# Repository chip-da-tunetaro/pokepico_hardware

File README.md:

# pokepico_hardware_MFT2019
pokepico rev.1のハードウェア

## 回路図
schematics.pdfを参照してください

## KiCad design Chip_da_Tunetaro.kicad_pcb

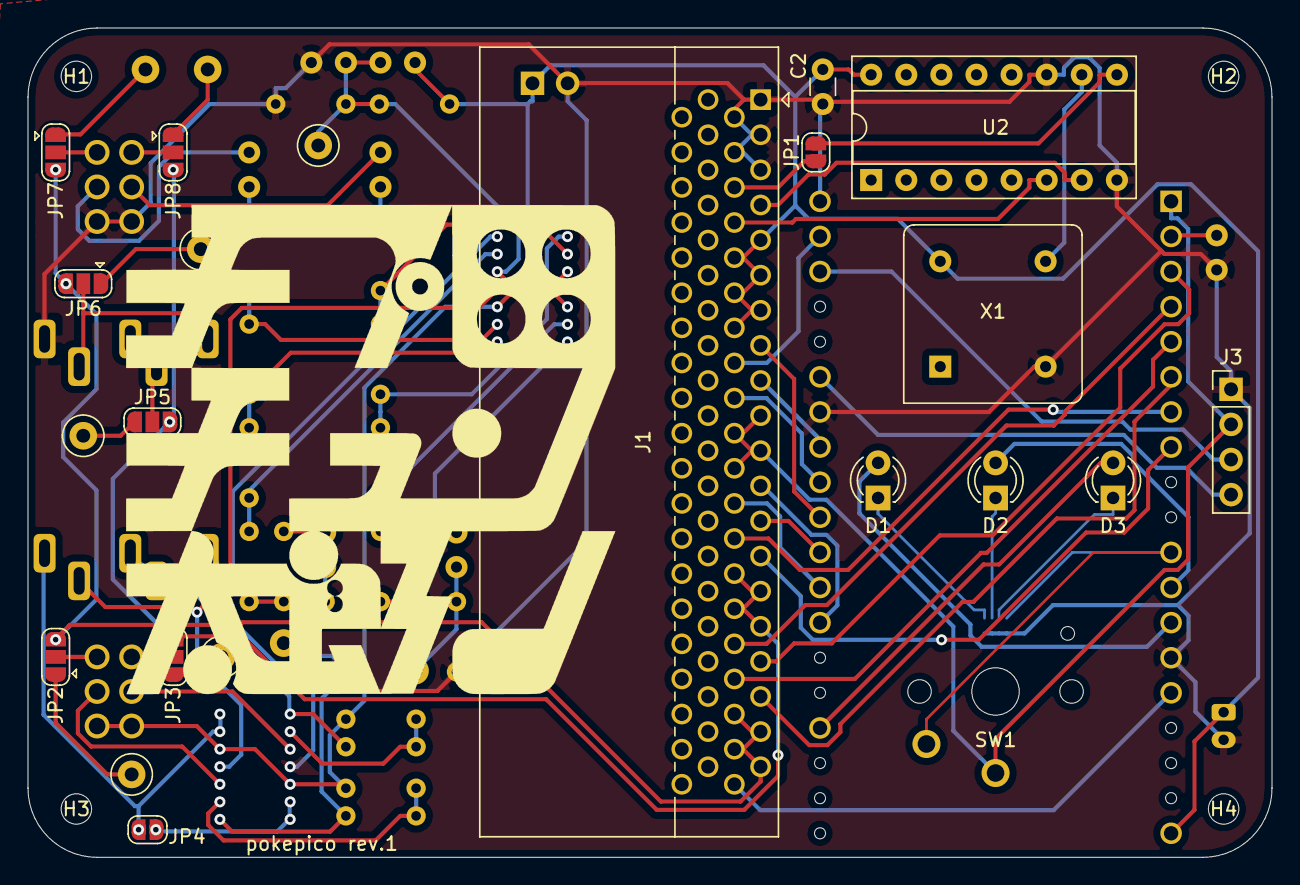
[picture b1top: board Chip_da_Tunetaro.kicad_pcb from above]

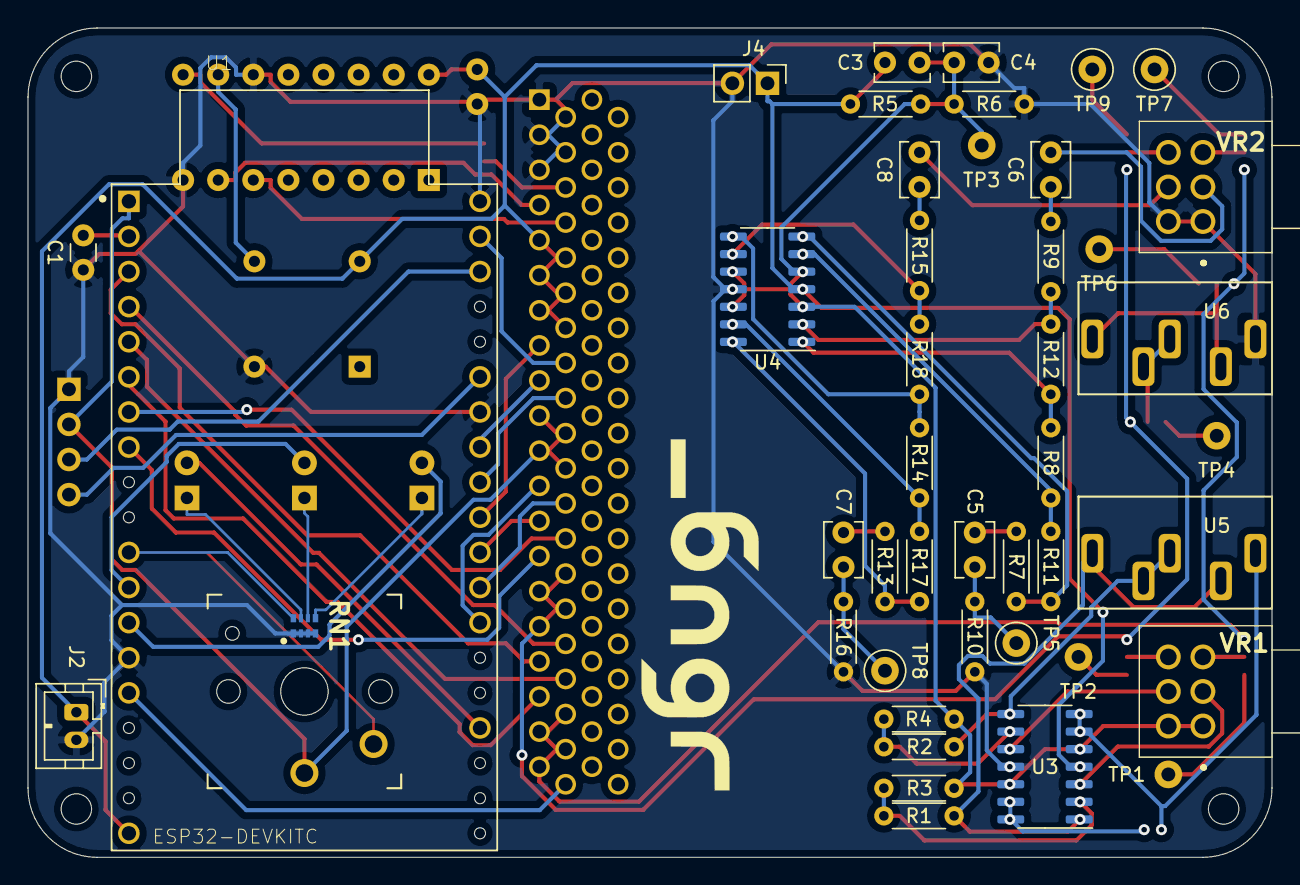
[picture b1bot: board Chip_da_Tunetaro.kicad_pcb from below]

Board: 2 copper layers, 90.0 x 60.0 mm, 66 parts (39 on the bottom side), 71 nets.

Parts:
C1: 1n; C_Disc_D3.0mm_W1.6mm_P2.50mm
C2: 0.1u; C_Disc_D3.0mm_W1.6mm_P2.50mm
C3, C4, C5, C6, C7, C8: C; C_Disc_D3.8mm_W2.6mm_P2.50mm
D1, D2, D3: LED; LED_D3.0mm
H1, H2, H3, H4: MountingHole; MountingHole_2.2mm_M2
J1: microbit_edge_connector; 4UCON_10156_2x40_P1.27mm_Socket_Horizontal
J2: Conn_01x02_Male; JST_PH_B2B-PH-K_1x02_P2.00mm_Vertical
J3: I2C; PinHeader_1x04_P2.54mm_Vertical
J4: POWERPOINT; PinHeader_1x02_P2.54mm_Vertical
JP1: SAA_INT_CLOCK; SolderJumper-2_P1.3mm_Open_RoundedPad1.0x1.5mm
JP2: FROW_L_SEL; SolderJumper-3_P1.3mm_Open_RoundedPad1.0x1.5mm
JP3: FLOW_R_SEL; SolderJumper-3_P1.3mm_Open_RoundedPad1.0x1.5mm
JP4: Jumper_NO_Small; SolderJumper-2_P1.3mm_Open_RoundedPad1.0x1.5mm
JP5: OUT_R_SEL; SolderJumper-3_P1.3mm_Open_RoundedPad1.0x1.5mm
JP6: OUT_L_SEL; SolderJumper-3_P1.3mm_Open_RoundedPad1.0x1.5mm
JP7: AMP_L_SEL; SolderJumper-3_P1.3mm_Open_RoundedPad1.0x1.5mm
JP8: AMP_R_SEL; SolderJumper-3_P1.3mm_Open_RoundedPad1.0x1.5mm
R1, R2, R3, R4, R5, R6, R7, R8, R9, R10, R11, R12, R13, R14, R15, R16, R17, R18: R; R_Axial_DIN0204_L3.6mm_D1.6mm_P5.08mm_Horizontal
RN1: MNR04MRAPJ103; RESCAX50P100X200X36-8N
SW1: SW_Push; PG1350
TP1: FLOW_L_ALT; TestPoint_Loop_D1.80mm_Drill1.0mm_Beaded
TP2: FLOW_R_ALT; TestPoint_Loop_D1.80mm_Drill1.0mm_Beaded
TP3: BIAS; TestPoint_Loop_D1.80mm_Drill1.0mm_Beaded
TP4: OUT_R_ALT; TestPoint_Loop_D1.80mm_Drill1.0mm_Beaded
TP5: LEFT_OUT; TestPoint_Loop_D1.80mm_Drill1.0mm_Beaded
TP6: OUT_L_ALT; TestPoint_Loop_D1.80mm_Drill1.0mm_Beaded
TP7: AMP_L_ALT; TestPoint_Loop_D1.80mm_Drill1.0mm_Beaded
TP8: RIGHT_OUT; TestPoint_Loop_D1.80mm_Drill1.0mm_Beaded
TP9: AMP_R_ALT; TestPoint_Loop_D1.80mm_Drill1.0mm_Beaded
U1: ESP32-DEVKITC
U2: 4040; DIP-16_W7.62mm_Socket
U3, U4: LMV324; SOIC-14_3.9x8.7mm_P1.27mm
U5, U6: PJ-325
VR1, VR2: RK0972A503L15F
X1: CXO_DIP8; Oscillator_DIP-8
gg1: LOGO; chip

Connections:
3V3: J1.37, J1.39, J1.41, J1.43, J3.2, SW1.1, U1.1
5V: C2.2, C3.1, J1.17, J1.19, J1.21, J1.23, J1.25, J1.27, J2.1, J4.1, R5.1, U1.19, U2.16, U3.4, U4.4, X1.8
16MHz: U2.10, X1.5
AMP_IN_L: C6.2, VR2.2
AMP_IN_R: C8.2, VR2.5
CHECK1: J1.67, U1.5
CHECK2: J1.69, U1.6
CHECK3: J1.63, U1.4
CHECK4: J1.65, U1.3
CLK_AY: J1.15, U2.6
CLK_SAA: JP1.2, U2.9
CLK_SN: J1.13, U2.7
CONTROL1: J1.47, U1.27
CONTROL2: J1.49, U1.28
CONTROL3: J1.51, U1.7
CONTROL4: J1.53, U1.8
DATA: J1.31, U1.37
FLOW_IN_L: U3.3, VR1.2
FLOW_IN_R: U3.10, VR1.5
FLOW_OUT_L: R1.1, U3.1, U5.4, U5.5
FLOW_OUT_R: R2.1, U3.8, U5.2, U5.3
FLOW_OUT_SHIELD: JP4.1, U3.6, U3.7, U5.1
GND: C1.1, C2.1, C4.2, J1.1, J1.3, J1.5, J1.7, J1.9, J2.2, J3.1, J4.2, R6.2, R10.1, R16.1, RN1.1, RN1.2, RN1.3, RN1.4, U1.14, U1.32, U1.38, U2.8, U2.11, U3.11, U4.11, U6.1, VR2.1, VR2.4, X1.4
LATCH: J1.33, U1.31
LED1: D1.2, U1.13
LED2: D2.2, U1.12
LED3: D3.2, U1.23
LEFT_IN: J1.71, J1.73, J1.75, J1.77, JP2.3, JP6.3, JP7.3
LEFT_OUT: C5.1, R10.2, TP5.1
MUDA1: J1.29, U1.29
MUDA2: J1.45, U1.26
MUDA3: J1.79, U1.15
unnamed: C1.2, U1.2
unnamed: C5.2, R7.1
unnamed: C6.1, R9.2
unnamed: C7.2, R13.1
unnamed: C8.1, R15.2
unnamed: D1.1, RN1.5
unnamed: D2.1, RN1.6
unnamed: D3.1, RN1.7
unnamed: J1.11, JP1.1
unnamed: JP2.1, TP1.1
unnamed: JP2.2, VR1.3
unnamed: JP3.1, TP2.1
unnamed: JP3.2, VR1.6
unnamed: JP4.2, U3.13, U3.14
unnamed: JP5.1, TP4.1
unnamed: JP5.2, U6.2, U6.3
unnamed: JP6.1, TP6.1
unnamed: JP6.2, U6.4, U6.5
unnamed: JP7.1, TP7.1
unnamed: JP7.2, VR2.3
unnamed: JP8.1, TP9.1
unnamed: JP8.2, VR2.6
unnamed: R1.2, R3.2, U3.2
unnamed: R2.2, R4.2, U3.9
unnamed: R7.2, R11.1, U4.7
unnamed: R8.1, R11.2, U4.6
unnamed: R8.2, R12.1, U4.1
unnamed: R9.1, R12.2, U4.2
unnamed: R13.2, R17.1, U4.14
unnamed: R14.1, R17.2, U4.13
unnamed: R14.2, R18.1, U4.8
unnamed: R15.1, R18.2, U4.9
RIGHT_IN: J1.55, J1.57, J1.59, J1.61, JP3.3, JP5.3, JP8.3
RIGHT_OUT: C7.1, R16.2, TP8.1
SCK: J1.35, U1.30
SCL: J3.3, U1.36
SDA: J3.4, U1.33
SW: RN1.8, SW1.2, U1.11
bias: C3.2, C4.1, R3.1, R4.1, R5.2, R6.1, TP3.1, U3.5, U3.12, U4.3, U4.5, U4.10, U4.12, VR1.1, VR1.4

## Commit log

2019-08-14 add files
